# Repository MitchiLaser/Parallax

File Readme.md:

# Parallax

Parallax is a cheap and simple but also powerful data acquisition system. The core of this device is a Raspberry Pi Pico which has multiple analog-to-digital converters. These can be used to measure analog voltages and stream the data directly to a PC for further processing and storing.

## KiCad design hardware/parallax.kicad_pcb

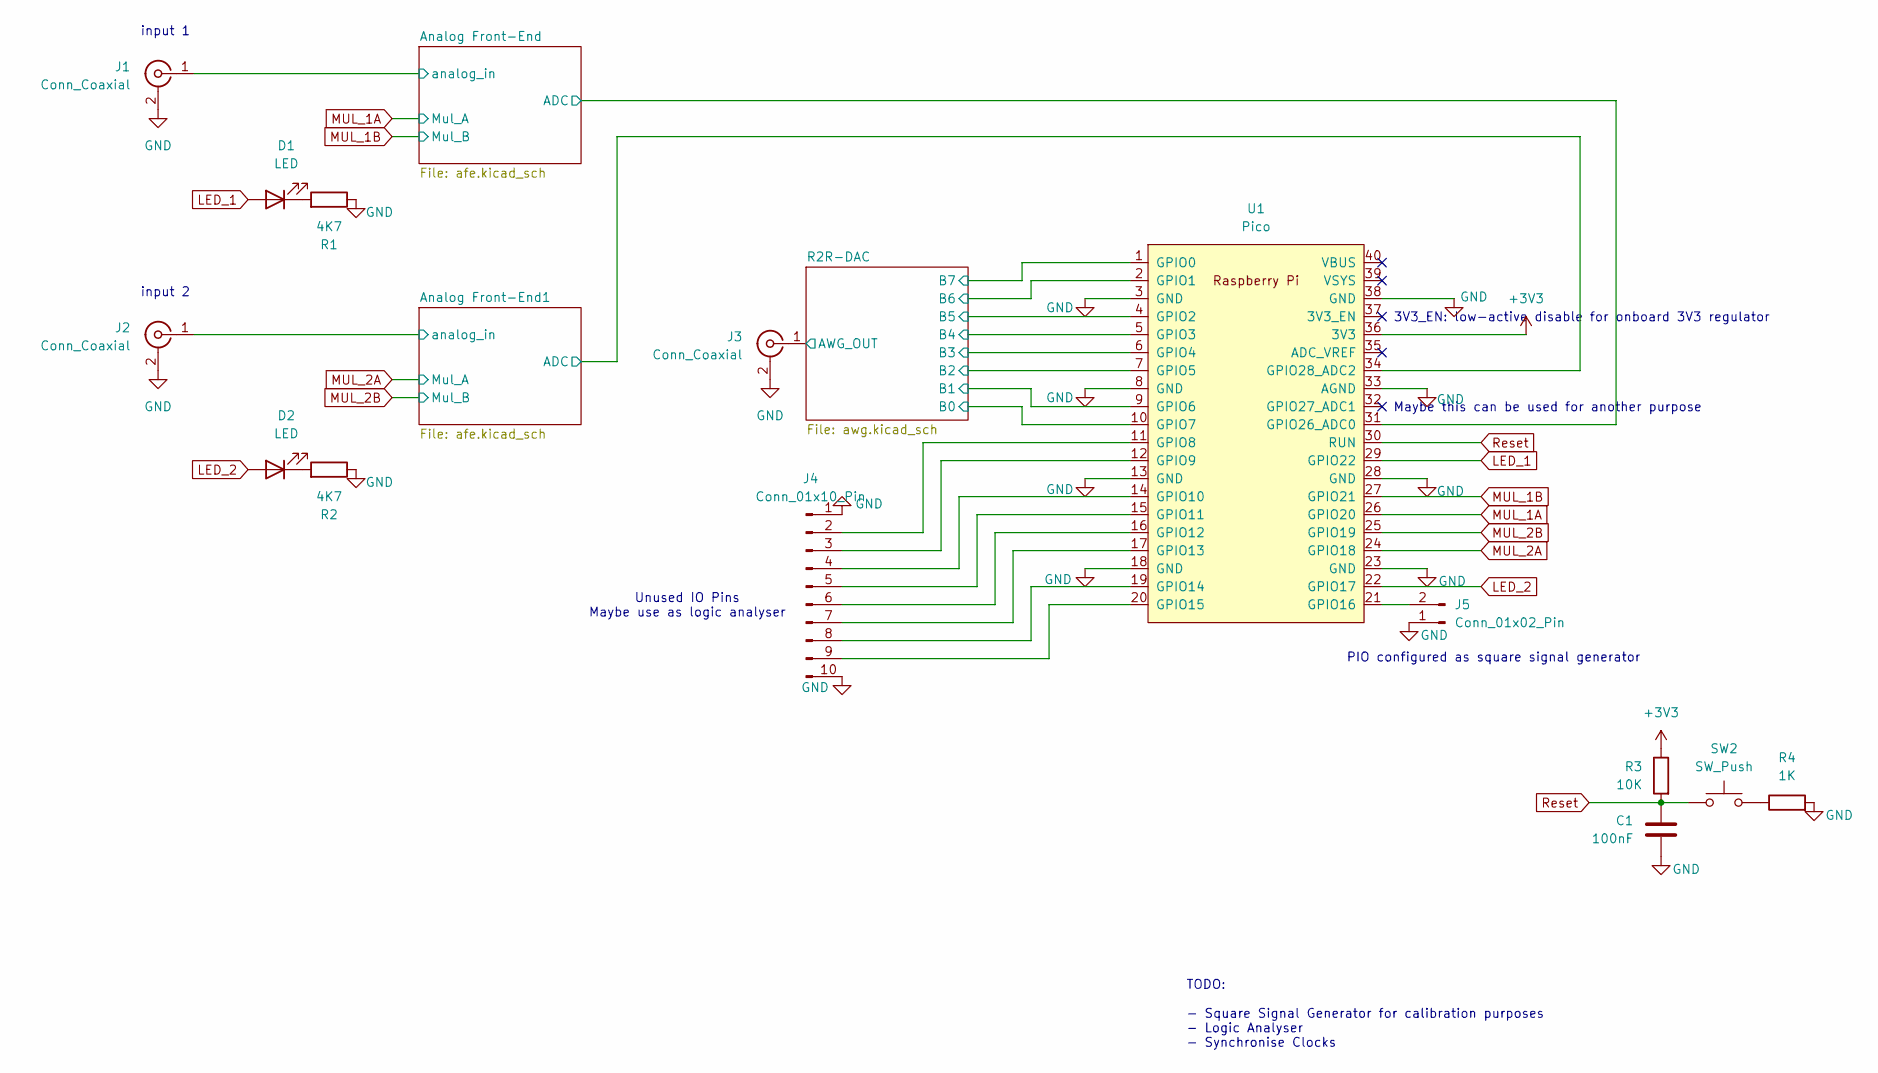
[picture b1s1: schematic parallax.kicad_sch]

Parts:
C1: 100nF; C_0603_1608Metric
D1, D2: LED; LED_0603_1608Metric_Pad1.05x0.95mm_HandSolder
J1, J2, J3: Conn_Coaxial; BNC_Amphenol_B6252HB-NPP3G-50_Horizontal
J4: Conn_01x10_Pin; PinHeader_1x10_P2.54mm_Vertical
J5: Conn_01x02_Pin; PinHeader_1x02_P2.54mm_Vertical
R1, R2: 4K7; R_0603_1608Metric
R3: 10K; R_0603_1608Metric
R4: 1K; R_0603_1608Metric
SW2: SW_Push; SW_PUSH_6mm_H4.3mm
U1: Pico; RaspberryPi_Pico_Common_Unspecified

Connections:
+3V3: R3.1, U1.36 (3V3); also elsewhere on the board
/Analog Front-End1/ADC: U1.34 (GPIO28_ADC2); also elsewhere on the board
/Analog Front-End1/analog_in: J2.1 (In); also elsewhere on the board
/Analog Front-End/ADC: U1.31 (GPIO26_ADC0); also elsewhere on the board
/Analog Front-End/analog_in: J1.1 (In); also elsewhere on the board
/R2R-DAC/AWG_OUT: J3.1 (In); also elsewhere on the board
/R2R-DAC/B0: U1.10 (GPIO7); also elsewhere on the board
/R2R-DAC/B1: U1.9 (GPIO6); also elsewhere on the board
/R2R-DAC/B2: U1.7 (GPIO5); also elsewhere on the board
/R2R-DAC/B3: U1.6 (GPIO4); also elsewhere on the board
/R2R-DAC/B4: U1.5 (GPIO3); also elsewhere on the board
/R2R-DAC/B5: U1.4 (GPIO2); also elsewhere on the board
/R2R-DAC/B6: U1.2 (GPIO1); also elsewhere on the board
/R2R-DAC/B7: U1.1 (GPIO0); also elsewhere on the board
GND: C1.2, J1.2 (Ext), J2.2 (Ext), J3.2 (Ext), J4.1, J4.10, J5.1, R1.1, R2.1, R4.2, U1.3 (GND), U1.8 (GND), U1.13 (GND), U1.18 (GND), U1.23 (GND), U1.28 (GND), U1.33 (AGND), U1.38 (GND); also elsewhere on the board
LED_1: D1.2 (A), U1.29 (GPIO22)
LED_2: D2.2 (A), U1.22 (GPIO17)
MUL_1A: U1.26 (GPIO20); also elsewhere on the board
MUL_1B: U1.27 (GPIO21); also elsewhere on the board
MUL_2A: U1.24 (GPIO18); also elsewhere on the board
MUL_2B: U1.25 (GPIO19); also elsewhere on the board
unnamed: D1.1 (K), R1.2
unnamed: D2.1 (K), R2.2
unnamed: J4.2, U1.11 (GPIO8)
unnamed: J4.3, U1.12 (GPIO9)
unnamed: J4.4, U1.14 (GPIO10)
unnamed: J4.5, U1.15 (GPIO11)
unnamed: J4.6, U1.16 (GPIO12)
unnamed: J4.7, U1.17 (GPIO13)
unnamed: J4.8, U1.19 (GPIO14)
unnamed: J4.9, U1.20 (GPIO15)
unnamed: J5.2, U1.21 (GPIO16)
unnamed: R4.1, SW2.2
Reset: C1.1, R3.2, SW2.1, U1.30 (RUN)

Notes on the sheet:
Unused IO Pins Maybe use as logic analyser
input 1
3V3_EN: low-active disable for onboard 3V3 regulator
Maybe this can be used for another purpose
input 2
TODO: - Square Signal Generator for calibration purposes - Logic Analyser - Synchronise Clocks
PIO configured as square signal generator

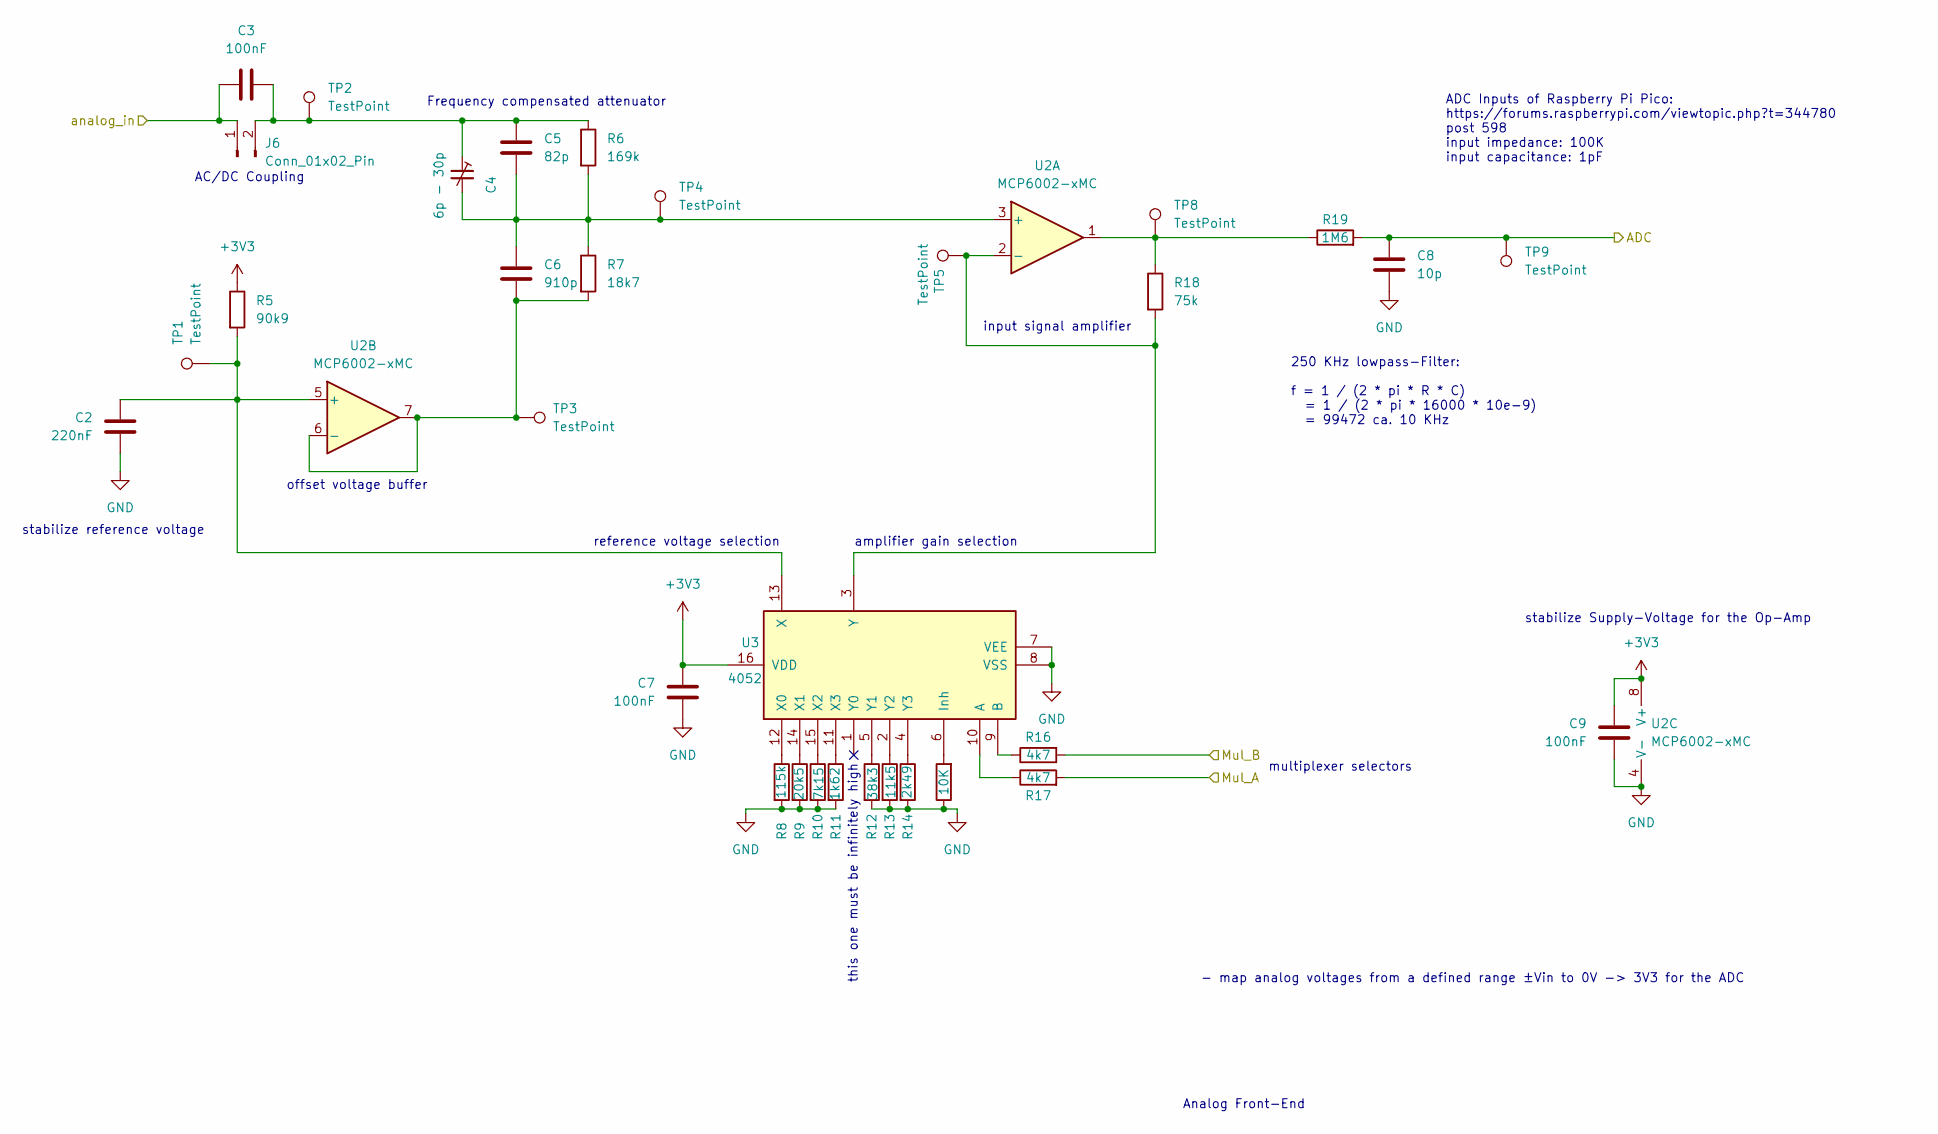
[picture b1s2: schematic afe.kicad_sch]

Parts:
C2: 220nF; C_0603_1608Metric
C3, C7, C9: 100nF; C_0603_1608Metric
C4: 6p - 30p; c_trim_D6mm_P5mm_1
C5: 82p; C_0603_1608Metric
C6: 910p; C_0603_1608Metric
C8: 10p; C_0603_1608Metric
J6: Conn_01x02_Pin; PinHeader_1x02_P2.54mm_Vertical
R5: 90k9; R_0603_1608Metric
R6: 169k; R_0603_1608Metric
R7: 18k7; R_0603_1608Metric
R8: 115k; R_0603_1608Metric
R9: 20k5; R_0603_1608Metric
R10: 7k15; R_0603_1608Metric
R11: 1k62; R_0603_1608Metric
R12: 38k3; R_0603_1608Metric
R13: 11k5; R_0603_1608Metric
R14: 2k49; R_0603_1608Metric
R15: 10K; R_0603_1608Metric
R16, R17: 4k7; R_0603_1608Metric
R18: 75k; R_0603_1608Metric
R19: 1M6; R_0603_1608Metric
TP1, TP2, TP3, TP4, TP5, TP8, TP9: TestPoint; TestPoint_Pad_D1.0mm
U2: MCP6002-xMC; DFN-8-1EP_3x2mm_P0.5mm_EP1.75x1.45mm
U3: 4052; SSOP-16_5.3x6.2mm_P0.65mm

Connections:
+3V3: C7.1, C9.1, R5.1, U2.8 (V+), U3.16 (VDD); also elsewhere on the board
/Analog Front-End/ADC: C8.1, R19.2, TP9.1 (1_1); also elsewhere on the board
/Analog Front-End/analog_in: C3.1, J6.1; also elsewhere on the board
GND: C2.2, C7.2, C8.2, C9.2, R8.2, R9.2, R10.2, R11.2, R12.2, R13.2, R14.2, R15.1, U2.4 (V-), U2.9 (V-), U3.7 (VEE), U3.8 (VSS); also elsewhere on the board
MUL_1A: R17.2; also elsewhere on the board
MUL_1B: R16.2; also elsewhere on the board
unnamed: C3.2, C4.1, C5.1, J6.2, R6.1, TP2.1 (1_1)
unnamed: R18.1, R19.1, TP8.1 (1_1), U2.1
unnamed: C4.2, C5.2, C6.1, R6.2, R7.1, TP4.1 (1_1), U2.3 (+)
unnamed: R18.2, TP5.1 (1_1), U2.2 (-), U3.3 (Y)
unnamed: C2.1, R5.2, TP1.1 (1_1), U2.5 (+), U3.13 (X)
unnamed: C6.2, R7.2, TP3.1 (1_1), U2.6 (-), U2.7
unnamed: R17.1, U3.10 (A)
unnamed: R16.1, U3.9 (B)
unnamed: R15.2, U3.6 (Inh)
unnamed: R8.1, U3.12 (X0)
unnamed: R9.1, U3.14 (X1)
unnamed: R10.1, U3.15 (X2)
unnamed: R11.1, U3.11 (X3)
unnamed: R12.1, U3.5 (Y1)
unnamed: R13.1, U3.2 (Y2)
unnamed: R14.1, U3.4 (Y3)

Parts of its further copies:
C10: 220nF; C_0603_1608Metric
C11, C15, C17: 100nF; C_0603_1608Metric
C12: 6p - 30p; c_trim_D6mm_P5mm_1
C13: 82p; C_0603_1608Metric
C14: 910p; C_0603_1608Metric
C16: 10p; C_0603_1608Metric
J7: Conn_01x02_Pin; PinHeader_1x02_P2.54mm_Vertical
R20: 90k9; R_0603_1608Metric
R21: 169k; R_0603_1608Metric
R22: 18k7; R_0603_1608Metric
R23: 115k; R_0603_1608Metric
R24: 20k5; R_0603_1608Metric
R25: 7k15; R_0603_1608Metric
R26: 1k62; R_0603_1608Metric
R27: 38k3; R_0603_1608Metric
R28: 11k5; R_0603_1608Metric
R29: 2k49; R_0603_1608Metric
R30: 10K; R_0603_1608Metric
R31, R32: 4k7; R_0603_1608Metric
R33: 75k; R_0603_1608Metric
R34: 1M6; R_0603_1608Metric
TP10, TP11, TP12, TP13, TP14, TP17, TP18: TestPoint; TestPoint_Pad_D1.0mm
U4: MCP6002-xMC; DFN-8-1EP_3x2mm_P0.5mm_EP1.75x1.45mm
U5: 4052; SSOP-16_5.3x6.2mm_P0.65mm

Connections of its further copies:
+3V3: C15.1, C17.1, R20.1, U4.8 (V+), U5.16 (VDD); also elsewhere on the board
/Analog Front-End1/ADC: C16.1, R34.2, TP18.1 (1_1); also elsewhere on the board
/Analog Front-End1/analog_in: C11.1, J7.1; also elsewhere on the board
GND: C10.2, C15.2, C16.2, C17.2, R23.2, R24.2, R25.2, R26.2, R27.2, R28.2, R29.2, R30.1, U4.4 (V-), U4.9 (V-), U5.7 (VEE), U5.8 (VSS); also elsewhere on the board
MUL_2A: R32.2; also elsewhere on the board
MUL_2B: R31.2; also elsewhere on the board
unnamed: C11.2, C12.1, C13.1, J7.2, R21.1, TP11.1 (1_1)
unnamed: R33.1, R34.1, TP17.1 (1_1), U4.1
unnamed: C12.2, C13.2, C14.1, R21.2, R22.1, TP13.1 (1_1), U4.3 (+)
unnamed: R33.2, TP14.1 (1_1), U4.2 (-), U5.3 (Y)
unnamed: C10.1, R20.2, TP10.1 (1_1), U4.5 (+), U5.13 (X)
unnamed: C14.2, R22.2, TP12.1 (1_1), U4.6 (-), U4.7
unnamed: R32.1, U5.10 (A)
unnamed: R31.1, U5.9 (B)
unnamed: R30.2, U5.6 (Inh)
unnamed: R23.1, U5.12 (X0)
unnamed: R24.1, U5.14 (X1)
unnamed: R25.1, U5.15 (X2)
unnamed: R26.1, U5.11 (X3)
unnamed: R27.1, U5.5 (Y1)
unnamed: R28.1, U5.2 (Y2)
unnamed: R29.1, U5.4 (Y3)

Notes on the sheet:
offset voltage buffer
250 KHz lowpass-Filter: f = 1 / (2 * pi * R * C) = 1 / (2 * pi * 16000 * 10e-9) = 99472 ca. 10 KHz
- map analog voltages from a defined range ±Vin to 0V -> 3V3 for the ADC
ADC Inputs of Raspberry Pi Pico: https://forums.raspberrypi.com/viewtopic.php?t=344780 post 598 input impedance: 100K input capacitance: 1pF
reference voltage selection
AC/DC Coupling
Frequency compensated attenuator
input signal amplifier
this one must be infinitely high
amplifier gain selection
Analog Front-End
stabilize Supply-Voltage for the Op-Amp
multiplexer selectors
stabilize reference voltage

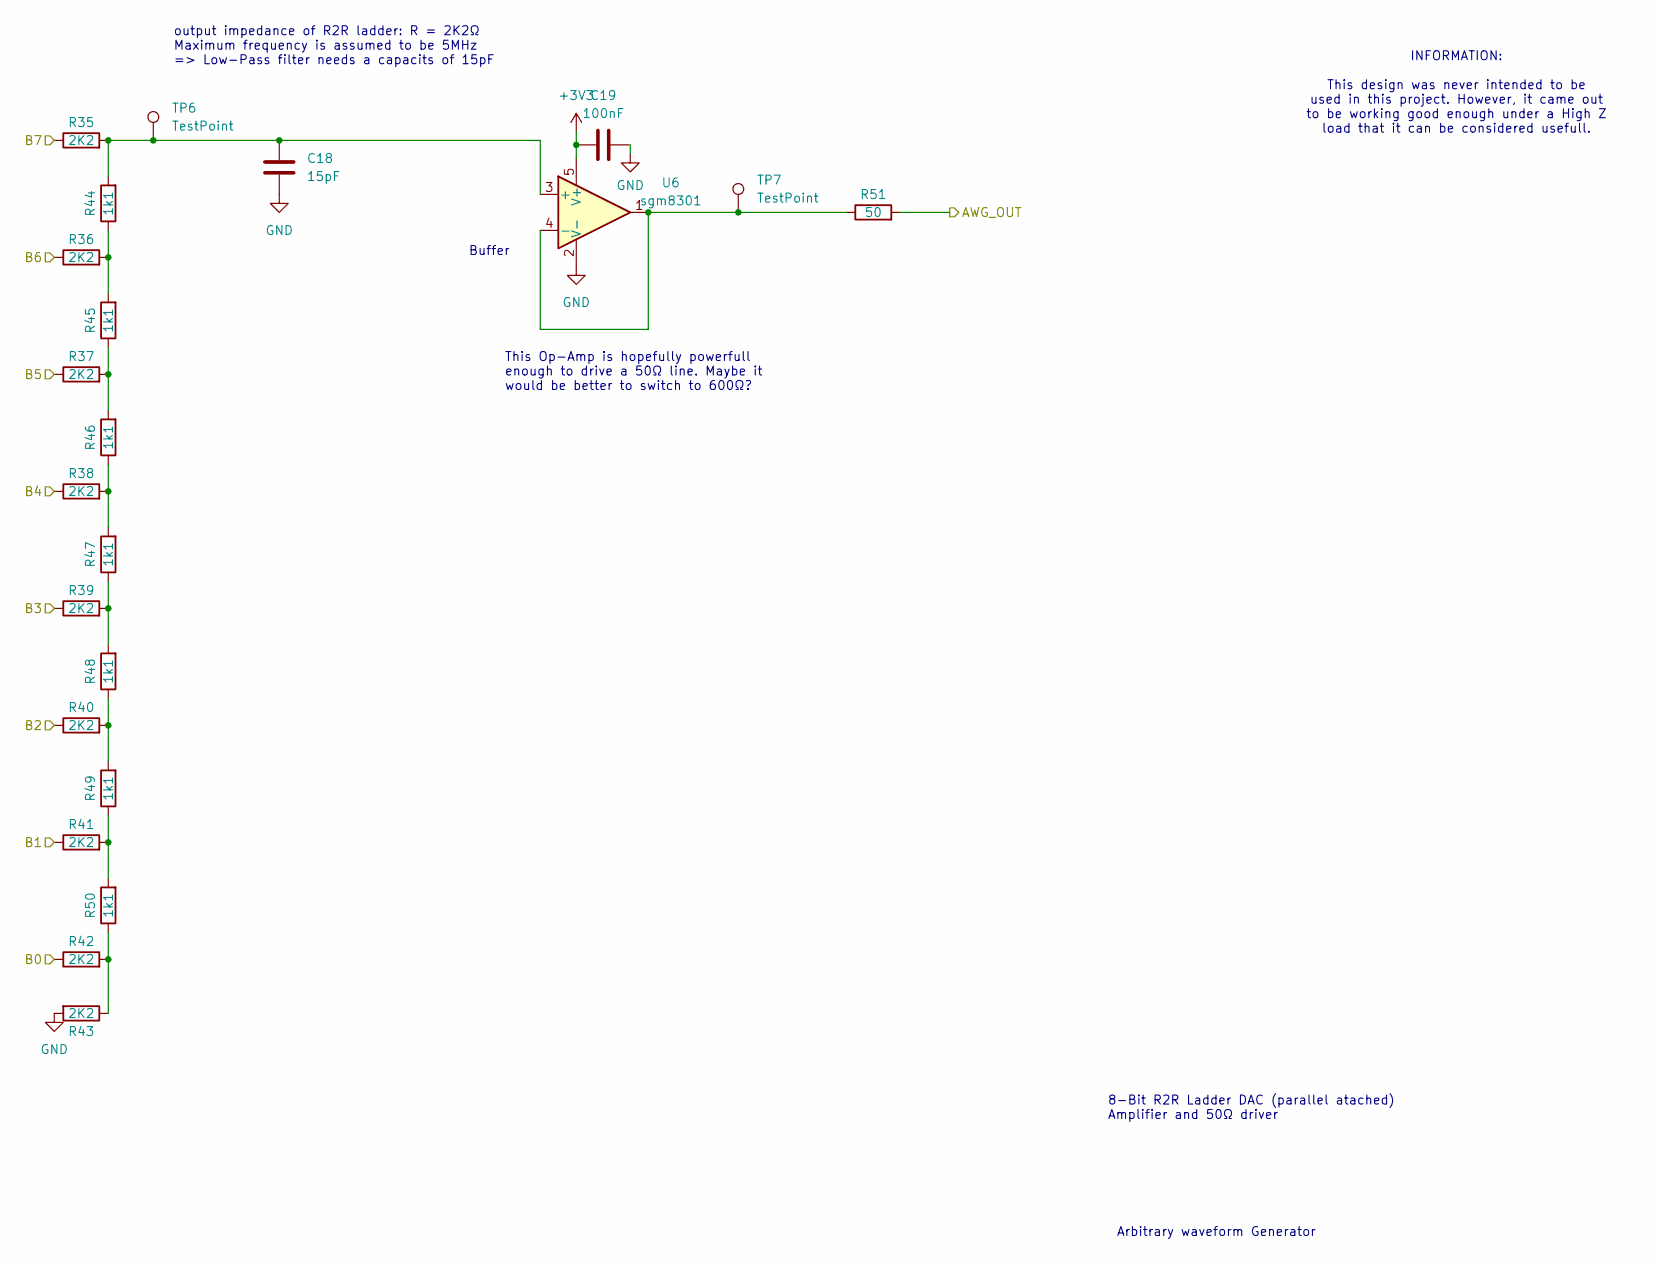
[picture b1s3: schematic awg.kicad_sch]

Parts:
C18: 15pF; C_0805_2012Metric_Pad1.18x1.45mm_HandSolder
C19: 100nF; C_0805_2012Metric_Pad1.18x1.45mm_HandSolder
R35, R36, R37, R38, R39, R40, R41, R42, R43: 2K2; R_0805_2012Metric_Pad1.20x1.40mm_HandSolder
R44, R45, R46, R47, R48, R49, R50: 1k1; R_0805_2012Metric_Pad1.20x1.40mm_HandSolder
R51: 50; R_0805_2012Metric_Pad1.20x1.40mm_HandSolder
TP6, TP7: TestPoint; TestPoint_Pad_D1.0mm
U6: sgm8301; SOT-23-5

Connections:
+3V3: C19.1, U6.5 (V+); also elsewhere on the board
/R2R-DAC/AWG_OUT: R51.2; also elsewhere on the board
/R2R-DAC/B0: R42.1; also elsewhere on the board
/R2R-DAC/B1: R41.1; also elsewhere on the board
/R2R-DAC/B2: R40.1; also elsewhere on the board
/R2R-DAC/B3: R39.1; also elsewhere on the board
/R2R-DAC/B4: R38.1; also elsewhere on the board
/R2R-DAC/B5: R37.1; also elsewhere on the board
/R2R-DAC/B6: R36.1; also elsewhere on the board
/R2R-DAC/B7: R35.1; also elsewhere on the board
GND: C18.1, C19.2, R43.2, U6.2 (V-); also elsewhere on the board
unnamed: R36.2, R44.1, R45.2
unnamed: R37.2, R45.1, R46.2
unnamed: R38.2, R46.1, R47.2
unnamed: R39.2, R47.1, R48.2
unnamed: R40.2, R48.1, R49.2
unnamed: R41.2, R49.1, R50.2
unnamed: R42.2, R43.1, R50.1
unnamed: C18.2, R35.2, R44.2, TP6.1 (1_1), U6.3 (+)
unnamed: R51.1, TP7.1 (1_1), U6.1, U6.4 (-)

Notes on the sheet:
Buffer
Arbitrary waveform Generator
8-Bit R2R Ladder DAC (parallel atached) Amplifier and 50Ω driver
This Op-Amp is hopefully powerfull enough to drive a 50Ω line. Maybe it would be better to switch to 600Ω?
INFORMATION: This design was never intended to be used in this project. However, it came out to be working good enough under a High Z load that it can be considered usefull.
output impedance of R2R ladder: R = 2K2Ω Maximum frequency is assumed to be 5MHz => Low-Pass filter needs a capacits of 15pF

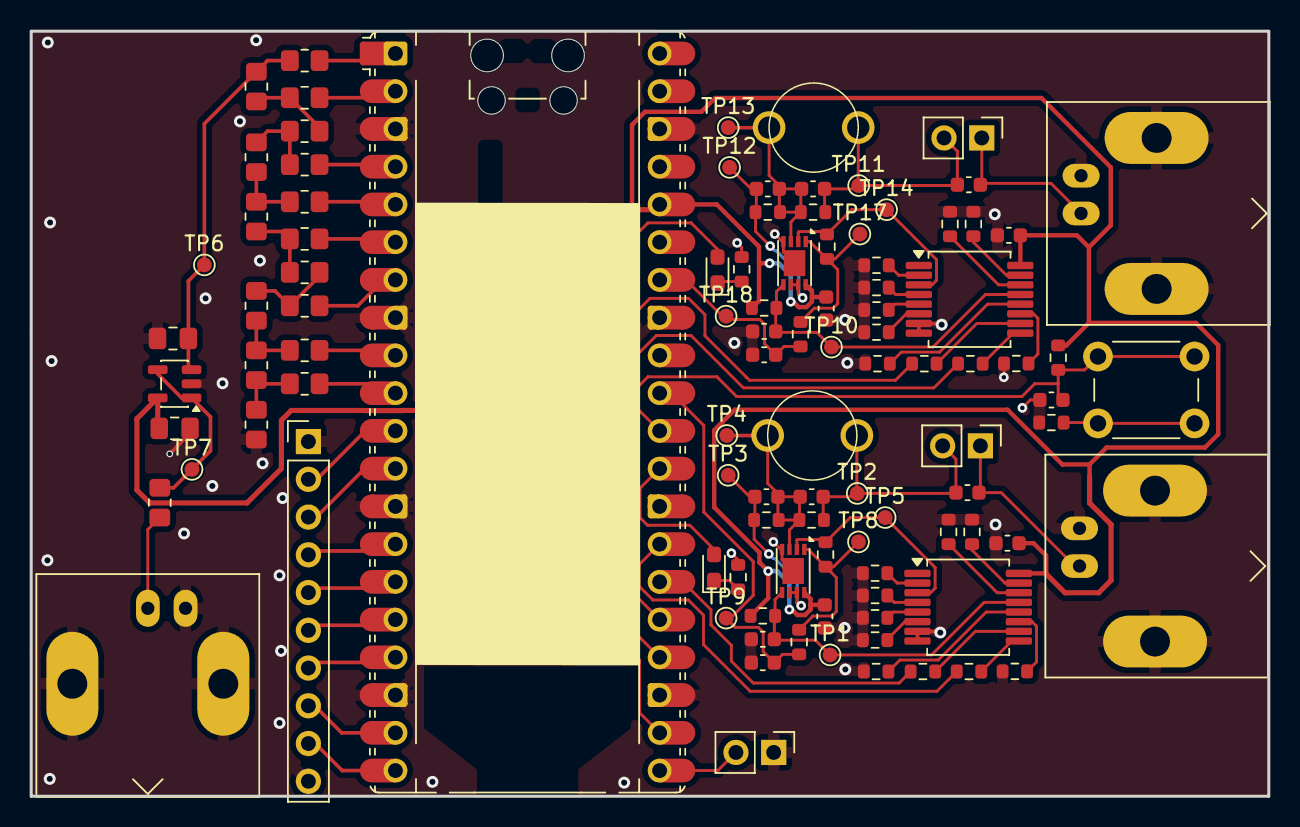
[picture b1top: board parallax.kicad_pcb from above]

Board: 2 copper layers, 83.3 x 51.5 mm, 102 parts (0 on the bottom side), 75 nets.

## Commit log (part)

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2022-10-12 like a version
2022-10-12 started with idea for experiment 21
2023-12-21 first steps in schematics design and hardware documentation introduction
2023-12-21 [docs] hardware chapter about simple attenuator
2023-12-21 updated .gitignore to ignore main.pdf
2023-12-21 [docs] chapter about capacitive attenuator
2023-12-21 restructuring chapterssections into separate .tex files
2023-12-22 [docs] frequency compensated attenuator
2024-01-31 [docs] voltage adder
2024-01-31 better structure of schematics
2024-02-01 [docs] beginning op-amp circuit
2024-02-01 [docs] op-amp chapter completed
2024-02-02 [docs] added chapter about clamping diodes
2024-02-02 [docs] added analog multiplexer information
2024-02-05 [docs] created files for later documentation topics
2024-02-05 github action test
2024-02-05 workflow next trial
2024-02-06 [docs] notation enhancement: introduced parallel operator
2024-02-06 started adding some footprints
2024-02-06 [hard] script to calculate resistor values based on defined input ranges
2024-02-07 [hard] beautified output of script to calculate resistor ratios
2024-02-07 [hard] resistor calculation: small improvement
2024-02-14 [docs] ESD protection section
2024-02-15 [docs] let the english speaking master rewrite everything
2024-02-15 action test
2024-02-15 [hard] footprint assignment and some Part Ordering numbers
2024-02-16 [docs] low pass filter
2024-02-16 restructured schematics, added more symbols and also some ordering part numbers
2024-02-17 [hard] simple dac design ready, integration still missing
2024-02-18 [awg] docs and schematics finished but integration not available
2024-02-19 [hw] afe: reoriented mux so a high-impedance option is available for op-amp 2
2025-06-20 simulation: Created SPICE model
2025-06-20 update analog front-end and resistor calculator: Better documentation
2025-06-20 calculate the right resistors for the circuit and the simulation
2025-06-20 update schematics to calculated values
2025-06-26 afe and simulation ready
2025-06-27 remove clamping diodes completely
2025-06-27 removed claping diodes from simulation
2026-01-13 started PCB routing, AFE ready, rest still in Progress
2026-02-15 Hardware: now in the state where a testing prototype can be ordered
